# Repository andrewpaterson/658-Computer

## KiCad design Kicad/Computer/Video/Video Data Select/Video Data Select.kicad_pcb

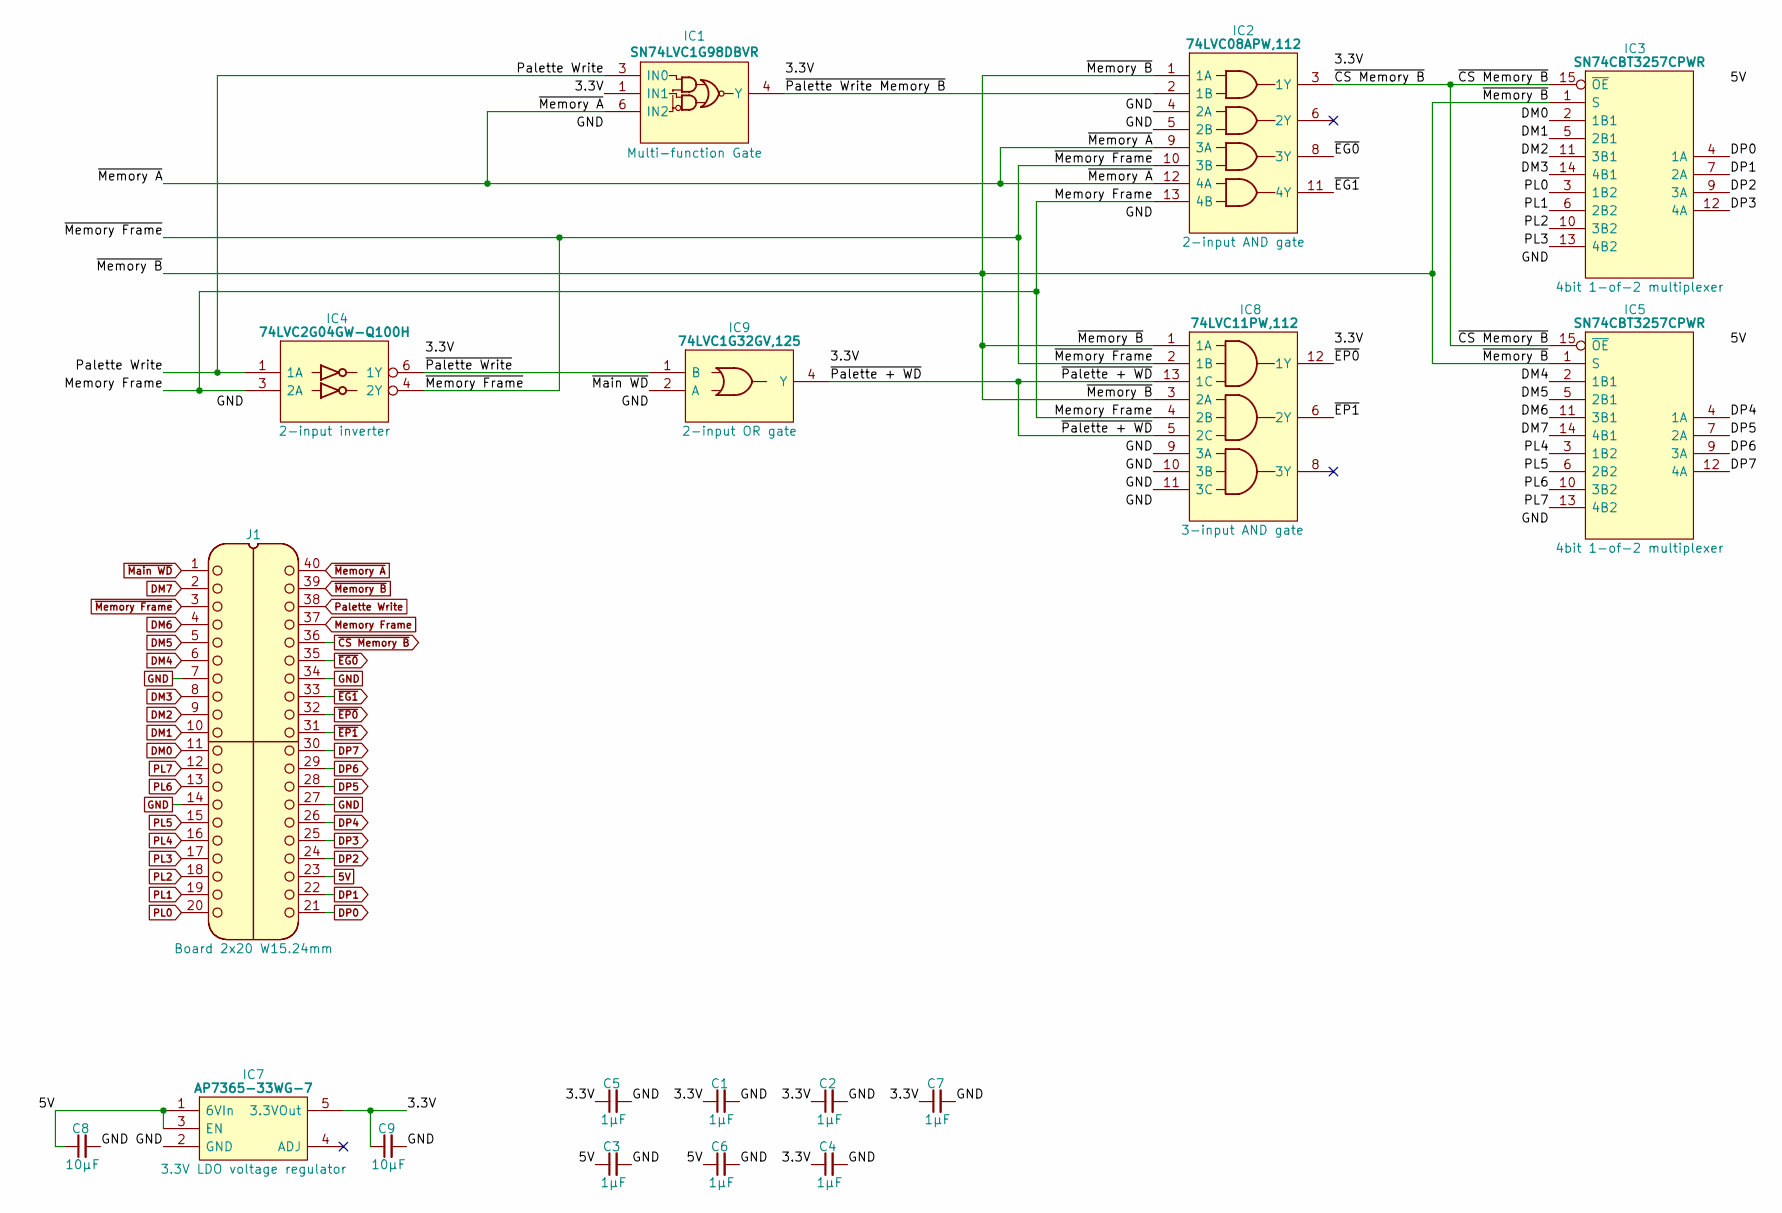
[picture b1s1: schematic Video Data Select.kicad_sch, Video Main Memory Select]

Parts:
C1, C2, C3, C4, C5, C6, C7: 1μF; C_0805
C8, C9: 10μF; C_0805
IC1: SN74LVC1G98DBVR; SOT95P280X145-6N; Manufacturer_Part_Number SN74LVC1G98DBVR; Mouser Part Number 595-SN74LVC1G98DBVR
IC2: 74LVC08APW,112; SOP65P640X110-14N; Manufacturer_Part_Number 74LVC08APW,112; Mouser Part Number 771-74LVC08APW
IC3, IC5: SN74CBT3257CPWR; SOP65P640X120-16N; Manufacturer_Part_Number SN74CBT3257CPWR; Mouser Part Number 595-SN74CBT3257CPWR
IC4: 74LVC2G04GW-Q100H; SOP65P210X110-6N; Manufacturer_Part_Number 74LVC2G04GW-Q100H; Mouser Part Number 771-74LVC2G04GWQ100H
IC7: AP7365-33WG-7; SOT95P285X130-5N; Manufacturer_Part_Number AP7365-33WG-7; Mouser Part Number 621-AP7365-33WG-7
IC8: 74LVC11PW,112; SOP65P640X110-14N; Mouser Part Number 771-LVC11PW112
IC9: 74LVC1G32GV,125; SOT95P275X110-5N; Manufacturer_Part_Number 74LVC1G32GV,125; Mouser Part Number 771-LVC1G32GV125
J1: Board 2x20 W15.24mm; DIP-40_Board_W15.24mm

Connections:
5V: C3.1, C6.1, C8.1, IC3.16 (5V), IC5.16 (5V), IC7.1 (6VIn), IC7.3 (EN), J1.23
/3.3V: C1.1, C2.1, C4.1, C5.1, C7.1, C9.1, IC1.1 (IN1), IC1.5 (3V), IC2.14 (3V), IC4.5 (3V), IC7.5 (3.3VOut), IC8.14 (3V), IC9.5 (3V)
/~Palette + WD: IC8.5 (2C), IC8.13 (1C), IC9.4 (Y)
/~Palette Write Memory B: IC1.4 (Y), IC2.2 (1B)
/~Palette Write: IC4.6 (1Y), IC9.1 (B)
DM0: IC3.2 (1B1), J1.11
DM1: IC3.5 (2B1), J1.10
DM2: IC3.11 (3B1), J1.9
DM3: IC3.14 (4B1), J1.8
DM4: IC5.2 (1B1), J1.6
DM5: IC5.5 (2B1), J1.5
DM6: IC5.11 (3B1), J1.4
DM7: IC5.14 (4B1), J1.2
DP0: IC3.4 (1A), J1.21
DP1: IC3.7 (2A), J1.22
DP2: IC3.9 (3A), J1.24
DP3: IC3.12 (4A), J1.25
DP4: IC5.4 (1A), J1.26
DP5: IC5.7 (2A), J1.28
DP6: IC5.9 (3A), J1.29
DP7: IC5.12 (4A), J1.30
GND: C1.2, C2.2, C3.2, C4.2, C5.2, C6.2, C7.2, C8.2, C9.2, IC1.2 (GND), IC2.4 (2A), IC2.5 (2B), IC2.7 (GND), IC3.8 (GND), IC4.2 (GND), IC5.8 (GND), IC7.2 (GND), IC8.7 (GND), IC8.9 (3A), IC8.10 (3B), IC8.11 (3C), IC9.3 (GND), J1.7, J1.14, J1.27, J1.34
Memory Frame: IC2.13 (4B), IC4.3 (2A), IC8.4 (2B), J1.37
PL0: IC3.3 (1B2), J1.20
PL1: IC3.6 (2B2), J1.19
PL2: IC3.10 (3B2), J1.18
PL3: IC3.13 (4B2), J1.17
PL4: IC5.3 (1B2), J1.16
PL5: IC5.6 (2B2), J1.15
PL6: IC5.10 (3B2), J1.13
PL7: IC5.13 (4B2), J1.12
Palette Write: IC1.3 (IN0), IC4.1 (1A), J1.38
~CS Memory B: IC2.3 (1Y), IC3.15 (~OE), IC5.15 (~OE), J1.36
~EG0: IC2.8 (3Y), J1.35
~EG1: IC2.11 (4Y), J1.33
~EP0: IC8.12 (1Y), J1.32
~EP1: IC8.6 (2Y), J1.31
~Main WD: IC9.2 (A), J1.1
~Memory A: IC1.6 (IN2), IC2.9 (3A), IC2.12 (4A), J1.40
~Memory B: IC2.1 (1A), IC3.1 (S), IC5.1 (S), IC8.1 (1A), IC8.3 (2A), J1.39
~Memory Frame: IC2.10 (3B), IC4.4 (2Y), IC8.2 (1B), J1.3

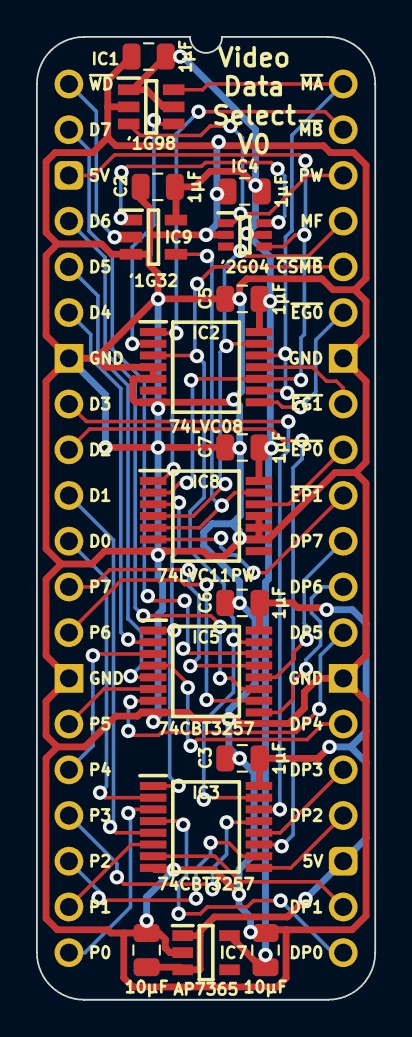
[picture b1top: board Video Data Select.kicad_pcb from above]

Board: 2 copper layers, 18.8 x 53.5 mm, 18 parts (0 on the bottom side), 41 nets.

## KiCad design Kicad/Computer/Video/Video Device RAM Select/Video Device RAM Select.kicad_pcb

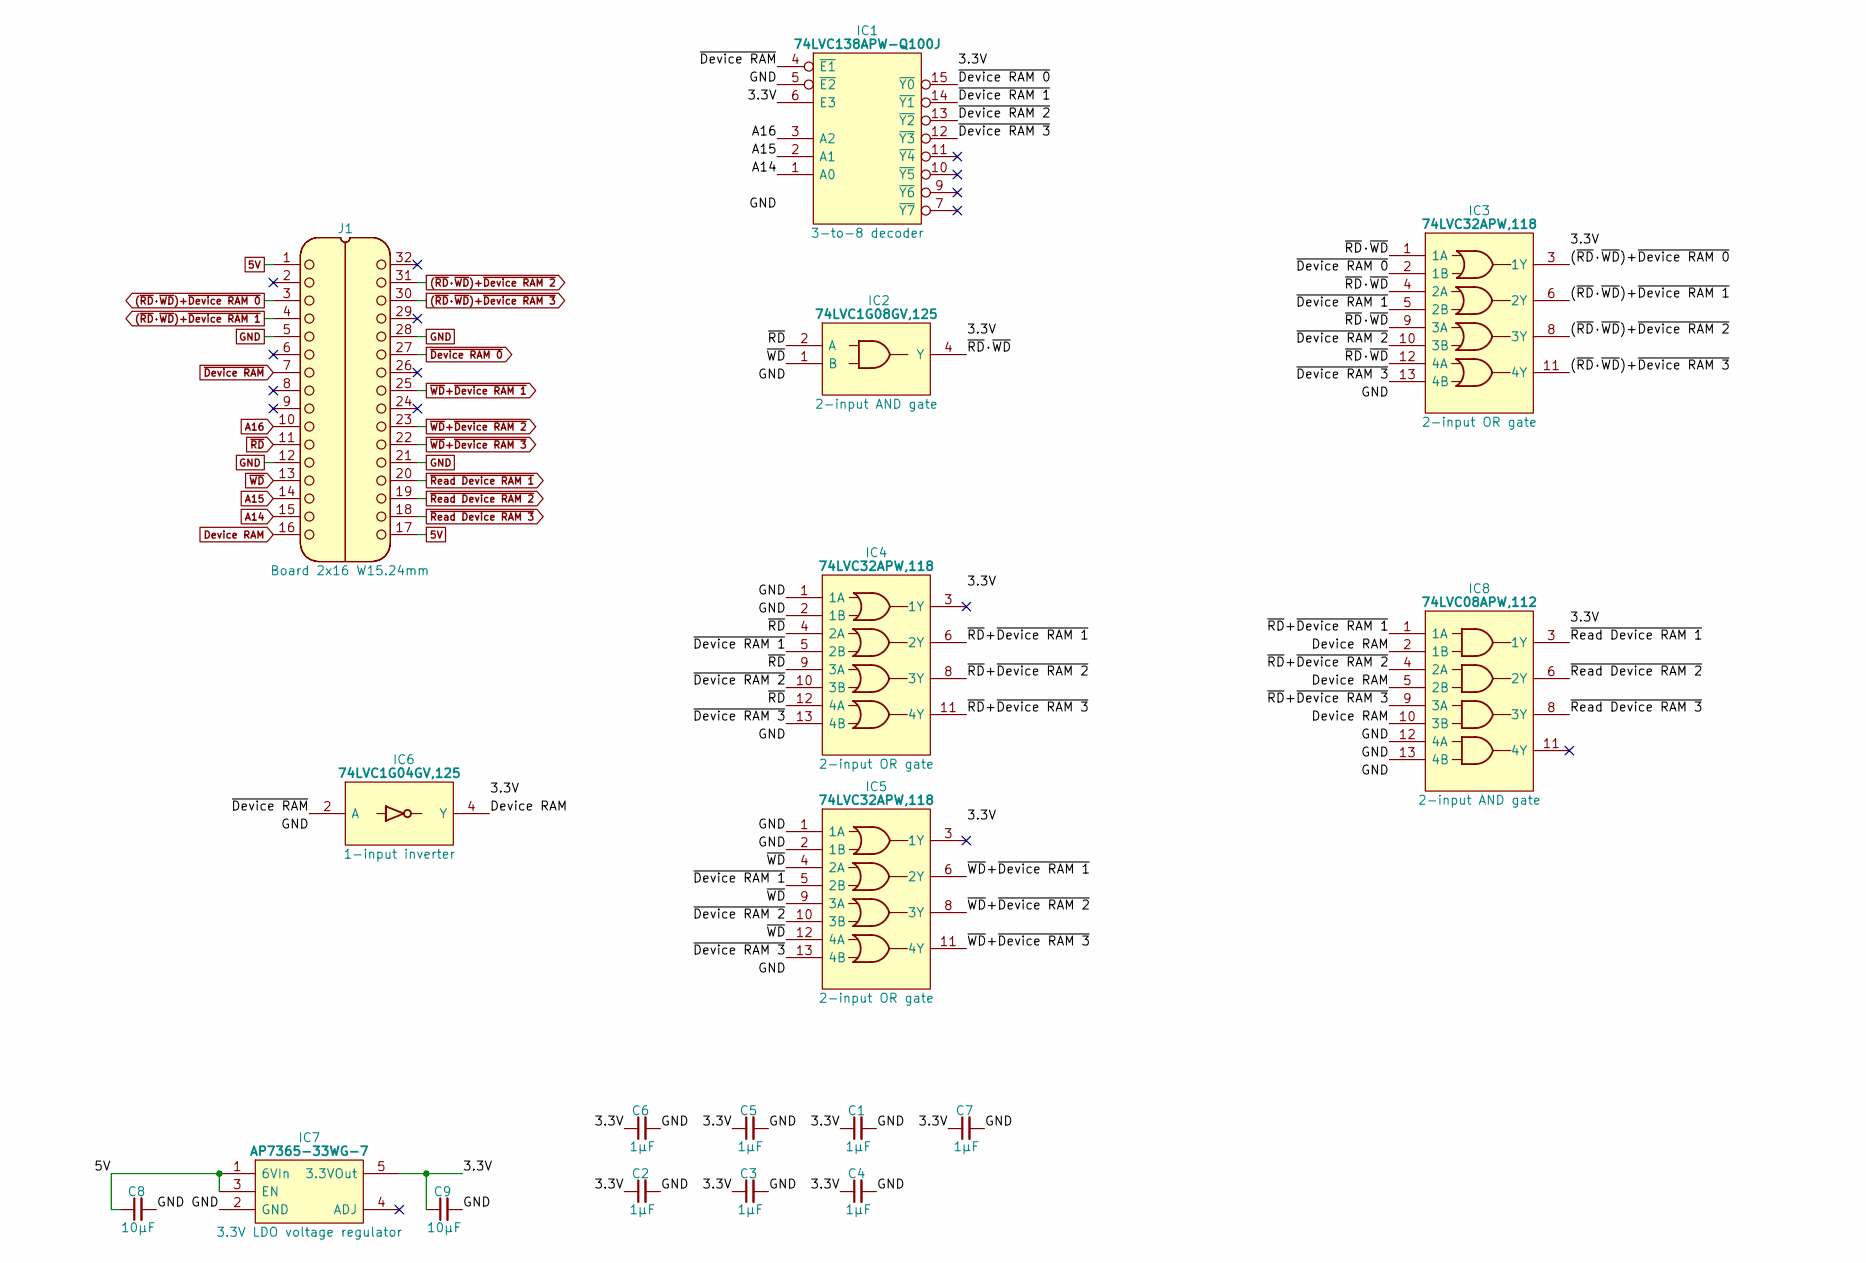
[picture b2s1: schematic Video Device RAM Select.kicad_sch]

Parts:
C1, C2, C3, C4, C5, C6, C7: 1μF; C_0805
C8, C9: 10µF; C_0805
IC1: 74LVC138APW-Q100J; SOP65P640X110-16N; Mouser Part Number 771-74LVC138APWQ100J
IC2: 74LVC1G08GV,125; SOT95P275X110-5N; Manufacturer_Part_Number 74LVC1G08GV,125; Mouser Part Number 771-74LVC1G08GV
IC3, IC4, IC5: 74LVC32APW,118; SOP65P640X110-14N; Manufacturer_Part_Number 74LVC32APW,118; Mouser Part Number 771-74LVC32APW-T
IC6: 74LVC1G04GV,125; SOT95P275X110-5N; Manufacturer_Part_Number 74LVC1G04GV,125; Mouser Part Number 771-74LVC1G04GV
IC7: AP7365-33WG-7; SOT95P285X130-5N; Manufacturer_Part_Number AP7365-33WG-7; Mouser Part Number 621-AP7365-33WG-7
IC8: 74LVC08APW,112; SOP65P640X110-14N; Manufacturer_Part_Number 74LVC08APW,112; Mouser Part Number 771-74LVC08APW
J1: Board 2x16 W15.24mm; DIP-32_Board_W15.24mm

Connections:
5V: C8.1, IC7.1 (6VIn), IC7.3 (EN), J1.1, J1.17
(~RD·~WD)+~Device RAM 0: IC3.3 (1Y), J1.3
(~RD·~WD)+~Device RAM 1: IC3.6 (2Y), J1.4
(~RD·~WD)+~Device RAM 2: IC3.8 (3Y), J1.31
(~RD·~WD)+~Device RAM 3: IC3.11 (4Y), J1.30
/3.3V: C1.1, C2.1, C3.1, C4.1, C5.1, C6.1, C7.1, C9.1, IC1.6 (E3), IC1.16 (3V), IC2.5 (3V), IC3.14 (3V), IC4.14 (3V), IC5.14 (3V), IC6.5 (3V), IC7.5 (3.3VOut), IC8.14 (3V)
/~Device RAM 1: IC1.14 (~Y1), IC3.5 (2B), IC4.5 (2B), IC5.5 (2B)
/~Device RAM 2: IC1.13 (~Y2), IC3.10 (3B), IC4.10 (3B), IC5.10 (3B)
/~Device RAM 3: IC1.12 (~Y3), IC3.13 (4B), IC4.13 (4B), IC5.13 (4B)
/~RD+~Device RAM 1: IC4.6 (2Y), IC8.1 (1A)
/~RD+~Device RAM 2: IC4.8 (3Y), IC8.4 (2A)
/~RD+~Device RAM 3: IC4.11 (4Y), IC8.9 (3A)
/~RD·~WD: IC2.4 (Y), IC3.1 (1A), IC3.4 (2A), IC3.9 (3A), IC3.12 (4A)
A14: IC1.1 (A0), J1.15
A15: IC1.2 (A1), J1.14
A16: IC1.3 (A2), J1.10
Device RAM: IC6.4 (Y), IC8.2 (1B), IC8.5 (2B), IC8.10 (3B), J1.16
GND: C1.2, C2.2, C3.2, C4.2, C5.2, C6.2, C7.2, C8.2, C9.2, IC1.5 (~E2), IC1.8 (GND), IC2.3 (GND), IC3.7 (GND), IC4.1 (1A), IC4.2 (1B), IC4.7 (GND), IC5.1 (1A), IC5.2 (1B), IC5.7 (GND), IC6.3 (GND), IC7.2 (GND), IC8.7 (GND), IC8.12 (4A), IC8.13 (4B), J1.5, J1.12, J1.21, J1.28
~Device RAM 0: IC1.15 (~Y0), IC3.2 (1B), J1.27
~Device RAM: IC1.4 (~E1), IC6.2 (A), J1.7
~RD: IC2.2 (A), IC4.4 (2A), IC4.9 (3A), IC4.12 (4A), J1.11
~Read Device RAM 1: IC8.3 (1Y), J1.20
~Read Device RAM 2: IC8.6 (2Y), J1.19
~Read Device RAM 3: IC8.8 (3Y), J1.18
~WD: IC2.1 (B), IC5.4 (2A), IC5.9 (3A), IC5.12 (4A), J1.13
~WD+~Device RAM 1: IC5.6 (2Y), J1.25
~WD+~Device RAM 2: IC5.8 (3Y), J1.23
~WD+~Device RAM 3: IC5.11 (4Y), J1.22

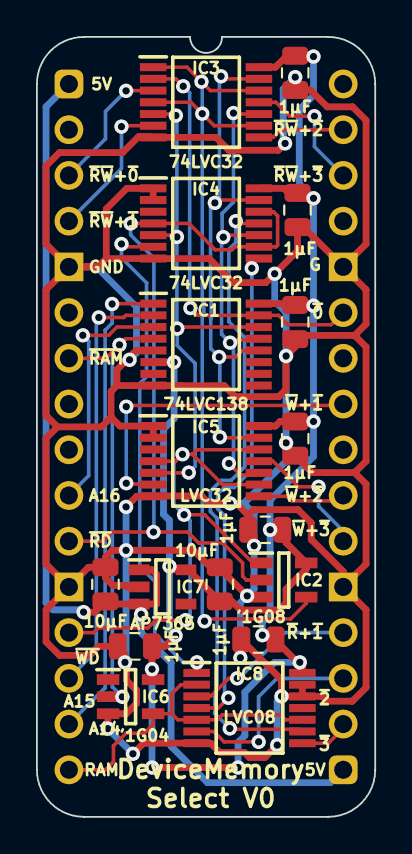
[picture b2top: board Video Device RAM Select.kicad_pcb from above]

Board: 2 copper layers, 18.8 x 43.3 mm, 18 parts (0 on the bottom side), 28 nets.

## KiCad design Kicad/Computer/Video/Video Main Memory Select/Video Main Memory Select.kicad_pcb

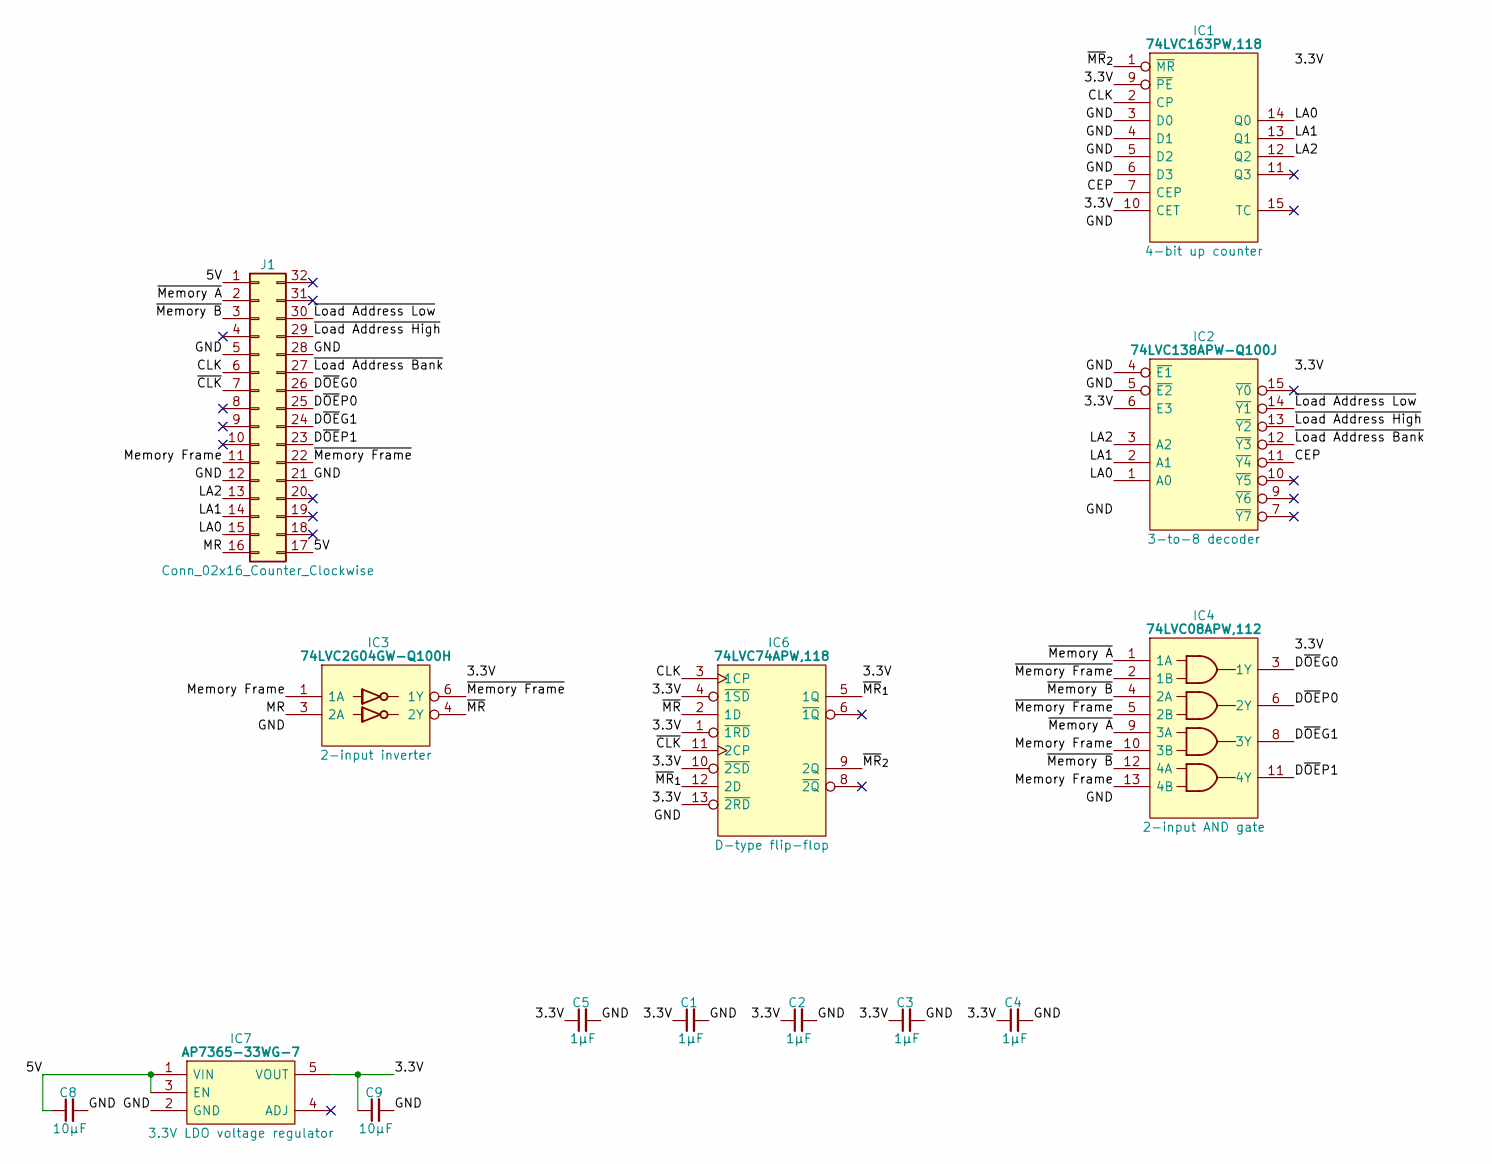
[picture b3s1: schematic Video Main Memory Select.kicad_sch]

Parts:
C1, C2, C3, C4, C5: 1μF; C_0805
C8, C9: 10µF; C_0805
IC1: 74LVC163PW,118; SOP65P640X110-16N; Mouser Part Number 771-74LVC163PW-T
IC2: 74LVC138APW-Q100J; SOP65P640X110-16N; Mouser Part Number 771-74LVC138APWQ100J
IC3: 74LVC2G04GW-Q100H; SOP65P210X110-6N; Manufacturer_Part_Number 74LVC2G04GW-Q100H; Mouser Part Number 771-74LVC2G04GWQ100H
IC4: 74LVC08APW,112; SOP65P640X110-14N; Manufacturer_Part_Number 74LVC08APW,112; Mouser Part Number 771-74LVC08APW
IC6: 74LVC74APW,118; SOP65P640X110-14N; Mouser Part Number 771-74LVC74APW-T
IC7: AP7365-33WG-7; SOT95P285X130-5N; Manufacturer_Part_Number AP7365-33WG-7; Mouser Part Number 621-AP7365-33WG-7
J1: Conn_02x16_Counter_Clockwise; DIP-32_Board_W15.24mm

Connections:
/3.3V: C1.1, C2.1, C3.1, C4.1, C5.1, C9.1, IC1.9 (~PE), IC1.10 (CET), IC1.16 (3V), IC2.6 (E3), IC2.16 (3V), IC3.5 (3V), IC4.14 (3V), IC6.1 (~1RD), IC6.4 (~1SD), IC6.10 (~2SD), IC6.13 (~2RD), IC6.14 (3V), IC7.5 (VOUT)
/5V: C8.1, IC7.1 (VIN), IC7.3 (EN), J1.1, J1.17
/CEP: IC1.7 (CEP), IC2.11 (~Y4)
/CLK: IC1.2 (CP), IC6.3 (1CP), J1.6
/D~OEG0: IC4.3 (1Y), J1.26
/D~OEG1: IC4.8 (3Y), J1.24
/D~OEP0: IC4.6 (2Y), J1.25
/D~OEP1: IC4.11 (4Y), J1.23
/GND: C1.2, C2.2, C3.2, C4.2, C5.2, C8.2, C9.2, IC1.3 (D0), IC1.4 (D1), IC1.5 (D2), IC1.6 (D3), IC1.8 (GND), IC2.4 (~E1), IC2.5 (~E2), IC2.8 (GND), IC3.2 (GND), IC4.7 (GND), IC6.7 (GND), IC7.2 (GND), J1.5, J1.12, J1.21, J1.28
/LA0: IC1.14 (Q0), IC2.1 (A0), J1.15
/LA1: IC1.13 (Q1), IC2.2 (A1), J1.14
/LA2: IC1.12 (Q2), IC2.3 (A2), J1.13
/MR: IC3.3 (2A), J1.16
/Memory Frame: IC3.1 (1A), IC4.10 (3B), IC4.13 (4B), J1.11
/~CLK: IC6.11 (2CP), J1.7
/~Load Address Bank: IC2.12 (~Y3), J1.27
/~Load Address High: IC2.13 (~Y2), J1.29
/~Load Address Low: IC2.14 (~Y1), J1.30
/~MR: IC3.4 (2Y), IC6.2 (1D)
/~MR_{1}: IC6.5 (1Q), IC6.12 (2D)
/~MR_{2}: IC1.1 (~MR), IC6.9 (2Q)
/~Memory A: IC4.1 (1A), IC4.9 (3A), J1.2
/~Memory B: IC4.4 (2A), IC4.12 (4A), J1.3
/~Memory Frame: IC3.6 (1Y), IC4.2 (1B), IC4.5 (2B), J1.22

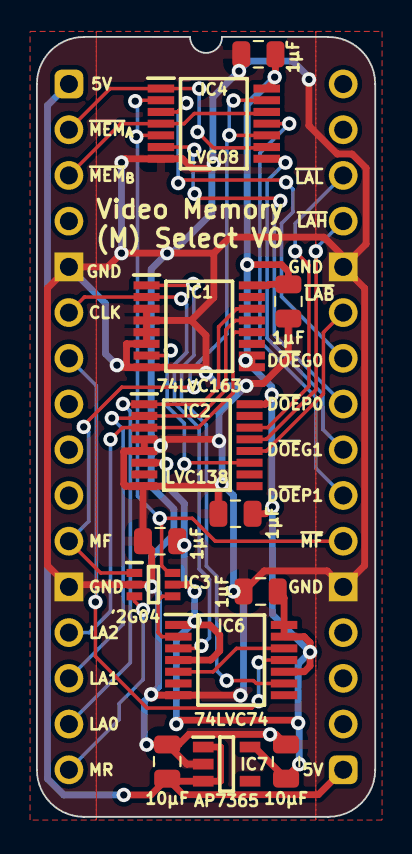
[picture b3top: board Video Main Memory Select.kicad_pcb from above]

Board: 2 copper layers, 18.8 x 43.3 mm, 14 parts (0 on the bottom side), 24 nets.

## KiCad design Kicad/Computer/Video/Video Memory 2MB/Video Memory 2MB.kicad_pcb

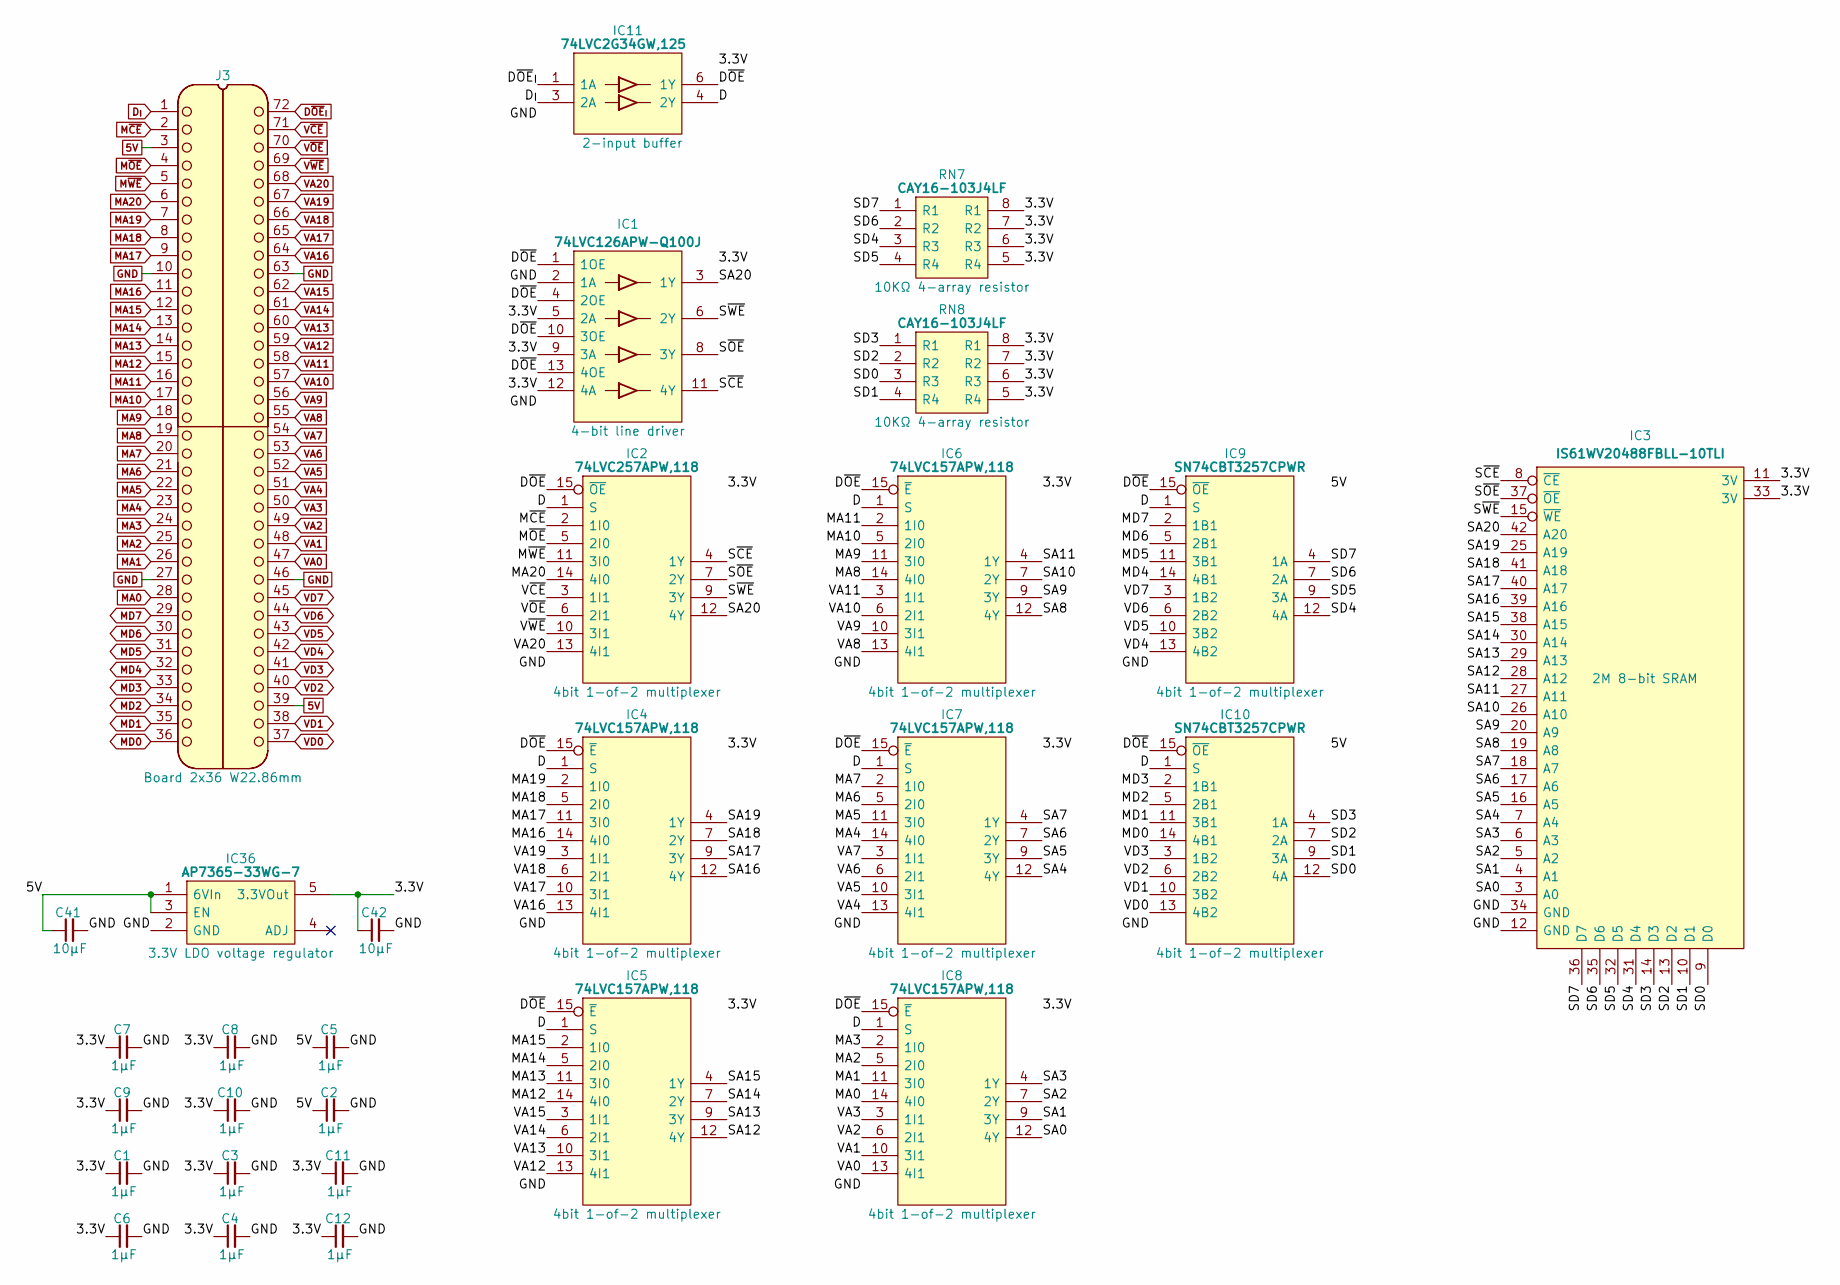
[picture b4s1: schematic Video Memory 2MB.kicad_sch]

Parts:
C1, C2, C3, C4, C5, C6, C7, C8, C9, C10, C11, C12: 1μF; C_0805
C41, C42: 10μF; C_0805
IC1: 74LVC126APW-Q100J; SOP65P640X110-14N; Mouser Part Number 771-74LVC126APW-Q100J
IC2: 74LVC257APW,118; SOP65P640X110-16N; Manufacturer_Part_Number 74LVC257APW,118; Mouser Part Number 771-74LVC257APW-T
IC3: IS61WV20488FBLL-10TLI; SOP80P1176X120-44N; Mouser Part Number 870-61W20488FBLL10TI
IC4, IC5, IC6, IC7, IC8: 74LVC157APW,118; SOP65P640X110-16N; Manufacturer_Part_Number 74LVC157APW,118; Mouser Part Number 771-74LVC157APW-T
IC9, IC10: SN74CBT3257CPWR; SOP65P640X120-16N; Manufacturer_Part_Number SN74CBT3257CPWR; Mouser Part Number 595-SN74CBT3257CPWR
IC11: 74LVC2G34GW,125; 74LVC2G34GW125; Manufacturer_Part_Number 74LVC2G34GW,125; Mouser Part Number 771-LVC2G34GW125
IC36: AP7365-33WG-7; SOT95P285X130-5N; Manufacturer_Part_Number AP7365-33WG-7; Mouser Part Number 621-AP7365-33WG-7
J3: Board 2x36 W22.86mm; DIP-72_Board_W22.86mm
RN7, RN8: CAY16-103J4LF; CAY16-J4; Manufacturer_Part_Number CAY16-103J4LF; Mouser Part Number 652-CAY16-103J4LF

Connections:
5V: C2.1, C5.1, C41.1, IC9.16 (5V), IC10.16 (5V), IC36.1 (6VIn), IC36.3 (EN), J3.3, J3.39
/3.3V: C1.1, C3.1, C4.1, C6.1, C7.1, C8.1, C9.1, C10.1, C11.1, C12.1, C42.1, IC1.5 (2A), IC1.9 (3A), IC1.12 (4A), IC1.14 (3V), IC2.16 (3V), IC3.11 (3V), IC3.33 (3V), IC4.16 (3V), IC5.16 (3V), IC6.16 (3V), IC7.16 (3V), IC8.16 (3V), IC11.5 (3V), IC36.5 (3.3VOut), RN7.5 (R4), RN7.6 (R3), RN7.7 (R2), RN7.8 (R1), RN8.5 (R4), RN8.6 (R3), RN8.7 (R2), RN8.8 (R1)
/D: IC2.1 (S), IC4.1 (S), IC5.1 (S), IC6.1 (S), IC7.1 (S), IC8.1 (S), IC9.1 (S), IC10.1 (S), IC11.4 (2Y)
/D~OE: IC1.1 (1OE), IC1.4 (2OE), IC1.10 (3OE), IC1.13 (4OE), IC2.15 (~OE), IC4.15 (~E), IC5.15 (~E), IC6.15 (~E), IC7.15 (~E), IC8.15 (~E), IC9.15 (~OE), IC10.15 (~OE), IC11.6 (1Y)
/SA0: IC3.3 (A0), IC8.12 (4Y)
/SA1: IC3.4 (A1), IC8.9 (3Y)
/SA2: IC3.5 (A2), IC8.7 (2Y)
/SA3: IC3.6 (A3), IC8.4 (1Y)
/SA4: IC3.7 (A4), IC7.12 (4Y)
/SA5: IC3.16 (A5), IC7.9 (3Y)
/SA6: IC3.17 (A6), IC7.7 (2Y)
/SA7: IC3.18 (A7), IC7.4 (1Y)
/SA8: IC3.19 (A8), IC6.12 (4Y)
/SA9: IC3.20 (A9), IC6.9 (3Y)
/SA10: IC3.26 (A10), IC6.7 (2Y)
/SA11: IC3.27 (A11), IC6.4 (1Y)
/SA12: IC3.28 (A12), IC5.12 (4Y)
/SA13: IC3.29 (A13), IC5.9 (3Y)
/SA14: IC3.30 (A14), IC5.7 (2Y)
/SA15: IC3.38 (A15), IC5.4 (1Y)
/SA16: IC3.39 (A16), IC4.12 (4Y)
/SA17: IC3.40 (A17), IC4.9 (3Y)
/SA18: IC3.41 (A18), IC4.7 (2Y)
/SA19: IC3.25 (A19), IC4.4 (1Y)
/SA20: IC1.3 (1Y), IC2.12 (4Y), IC3.42 (A20)
/SD0: IC3.9 (D0), IC10.12 (4A), RN8.3 (R3)
/SD1: IC3.10 (D1), IC10.9 (3A), RN8.4 (R4)
/SD2: IC3.13 (D2), IC10.7 (2A), RN8.2 (R2)
/SD3: IC3.14 (D3), IC10.4 (1A), RN8.1 (R1)
/SD4: IC3.31 (D4), IC9.12 (4A), RN7.3 (R3)
/SD5: IC3.32 (D5), IC9.9 (3A), RN7.4 (R4)
/SD6: IC3.35 (D6), IC9.7 (2A), RN7.2 (R2)
/SD7: IC3.36 (D7), IC9.4 (1A), RN7.1 (R1)
/S~CE: IC1.11 (4Y), IC2.4 (1Y), IC3.8 (~CE)
/S~OE: IC1.8 (3Y), IC2.7 (2Y), IC3.37 (~OE)
/S~WE: IC1.6 (2Y), IC2.9 (3Y), IC3.15 (~WE)
D_{I}: IC11.3 (2A), J3.1
D~OE_{I}: IC11.1 (1A), J3.72
GND: C1.2, C2.2, C3.2, C4.2, C5.2, C6.2, C7.2, C8.2, C9.2, C10.2, C11.2, C12.2, C41.2, C42.2, IC1.2 (1A), IC1.7 (GND), IC2.8 (GND), IC3.12 (GND), IC3.34 (GND), IC4.8 (GND), IC5.8 (GND), IC6.8 (GND), IC7.8 (GND), IC8.8 (GND), IC9.8 (GND), IC10.8 (GND), IC11.2 (GND), IC36.2 (GND), J3.10, J3.27, J3.46, J3.63
MA0: IC8.14 (4I0), J3.28
MA1: IC8.11 (3I0), J3.26
MA2: IC8.5 (2I0), J3.25
MA3: IC8.2 (1I0), J3.24
MA4: IC7.14 (4I0), J3.23
MA5: IC7.11 (3I0), J3.22
MA6: IC7.5 (2I0), J3.21
MA7: IC7.2 (1I0), J3.20
MA8: IC6.14 (4I0), J3.19
MA9: IC6.11 (3I0), J3.18
MA10: IC6.5 (2I0), J3.17
MA11: IC6.2 (1I0), J3.16
MA12: IC5.14 (4I0), J3.15
MA13: IC5.11 (3I0), J3.14
MA14: IC5.5 (2I0), J3.13
MA15: IC5.2 (1I0), J3.12
MA16: IC4.14 (4I0), J3.11
MA17: IC4.11 (3I0), J3.9
MA18: IC4.5 (2I0), J3.8
MA19: IC4.2 (1I0), J3.7
MA20: IC2.14 (4I0), J3.6
MD0: IC10.14 (4B1), J3.36
MD1: IC10.11 (3B1), J3.35
MD2: IC10.5 (2B1), J3.34
MD3: IC10.2 (1B1), J3.33
MD4: IC9.14 (4B1), J3.32
MD5: IC9.11 (3B1), J3.31
MD6: IC9.5 (2B1), J3.30
MD7: IC9.2 (1B1), J3.29
M~CE: IC2.2 (1I0), J3.2
M~OE: IC2.5 (2I0), J3.4
M~WE: IC2.11 (3I0), J3.5
VA0: IC8.13 (4I1), J3.47
VA1: IC8.10 (3I1), J3.48
VA2: IC8.6 (2I1), J3.49
VA3: IC8.3 (1I1), J3.50
VA4: IC7.13 (4I1), J3.51
VA5: IC7.10 (3I1), J3.52
VA6: IC7.6 (2I1), J3.53
VA7: IC7.3 (1I1), J3.54
VA8: IC6.13 (4I1), J3.55
VA9: IC6.10 (3I1), J3.56
VA10: IC6.6 (2I1), J3.57
VA11: IC6.3 (1I1), J3.58
VA12: IC5.13 (4I1), J3.59
VA13: IC5.10 (3I1), J3.60
VA14: IC5.6 (2I1), J3.61
VA15: IC5.3 (1I1), J3.62
VA16: IC4.13 (4I1), J3.64
VA17: IC4.10 (3I1), J3.65
VA18: IC4.6 (2I1), J3.66
VA19: IC4.3 (1I1), J3.67
VA20: IC2.13 (4I1), J3.68
VD0: IC10.13 (4B2), J3.37
VD1: IC10.10 (3B2), J3.38
VD2: IC10.6 (2B2), J3.40
VD3: IC10.3 (1B2), J3.41
VD4: IC9.13 (4B2), J3.42
VD5: IC9.10 (3B2), J3.43
VD6: IC9.6 (2B2), J3.44
VD7: IC9.3 (1B2), J3.45
V~CE: IC2.3 (1I1), J3.71
V~OE: IC2.6 (2I1), J3.70
V~WE: IC2.10 (3I1), J3.69

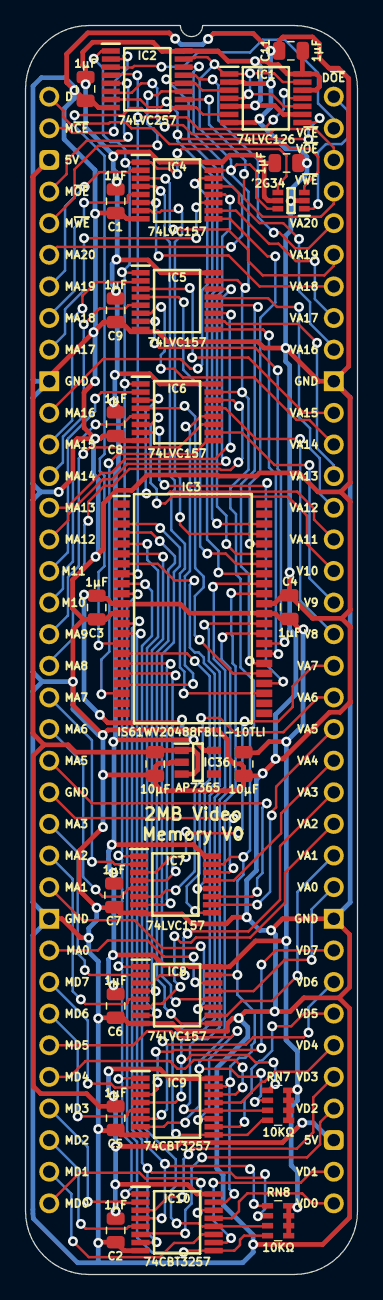
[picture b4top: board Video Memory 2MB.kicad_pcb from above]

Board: 2 copper layers, 26.7 x 100.3 mm, 29 parts (0 on the bottom side), 103 nets.

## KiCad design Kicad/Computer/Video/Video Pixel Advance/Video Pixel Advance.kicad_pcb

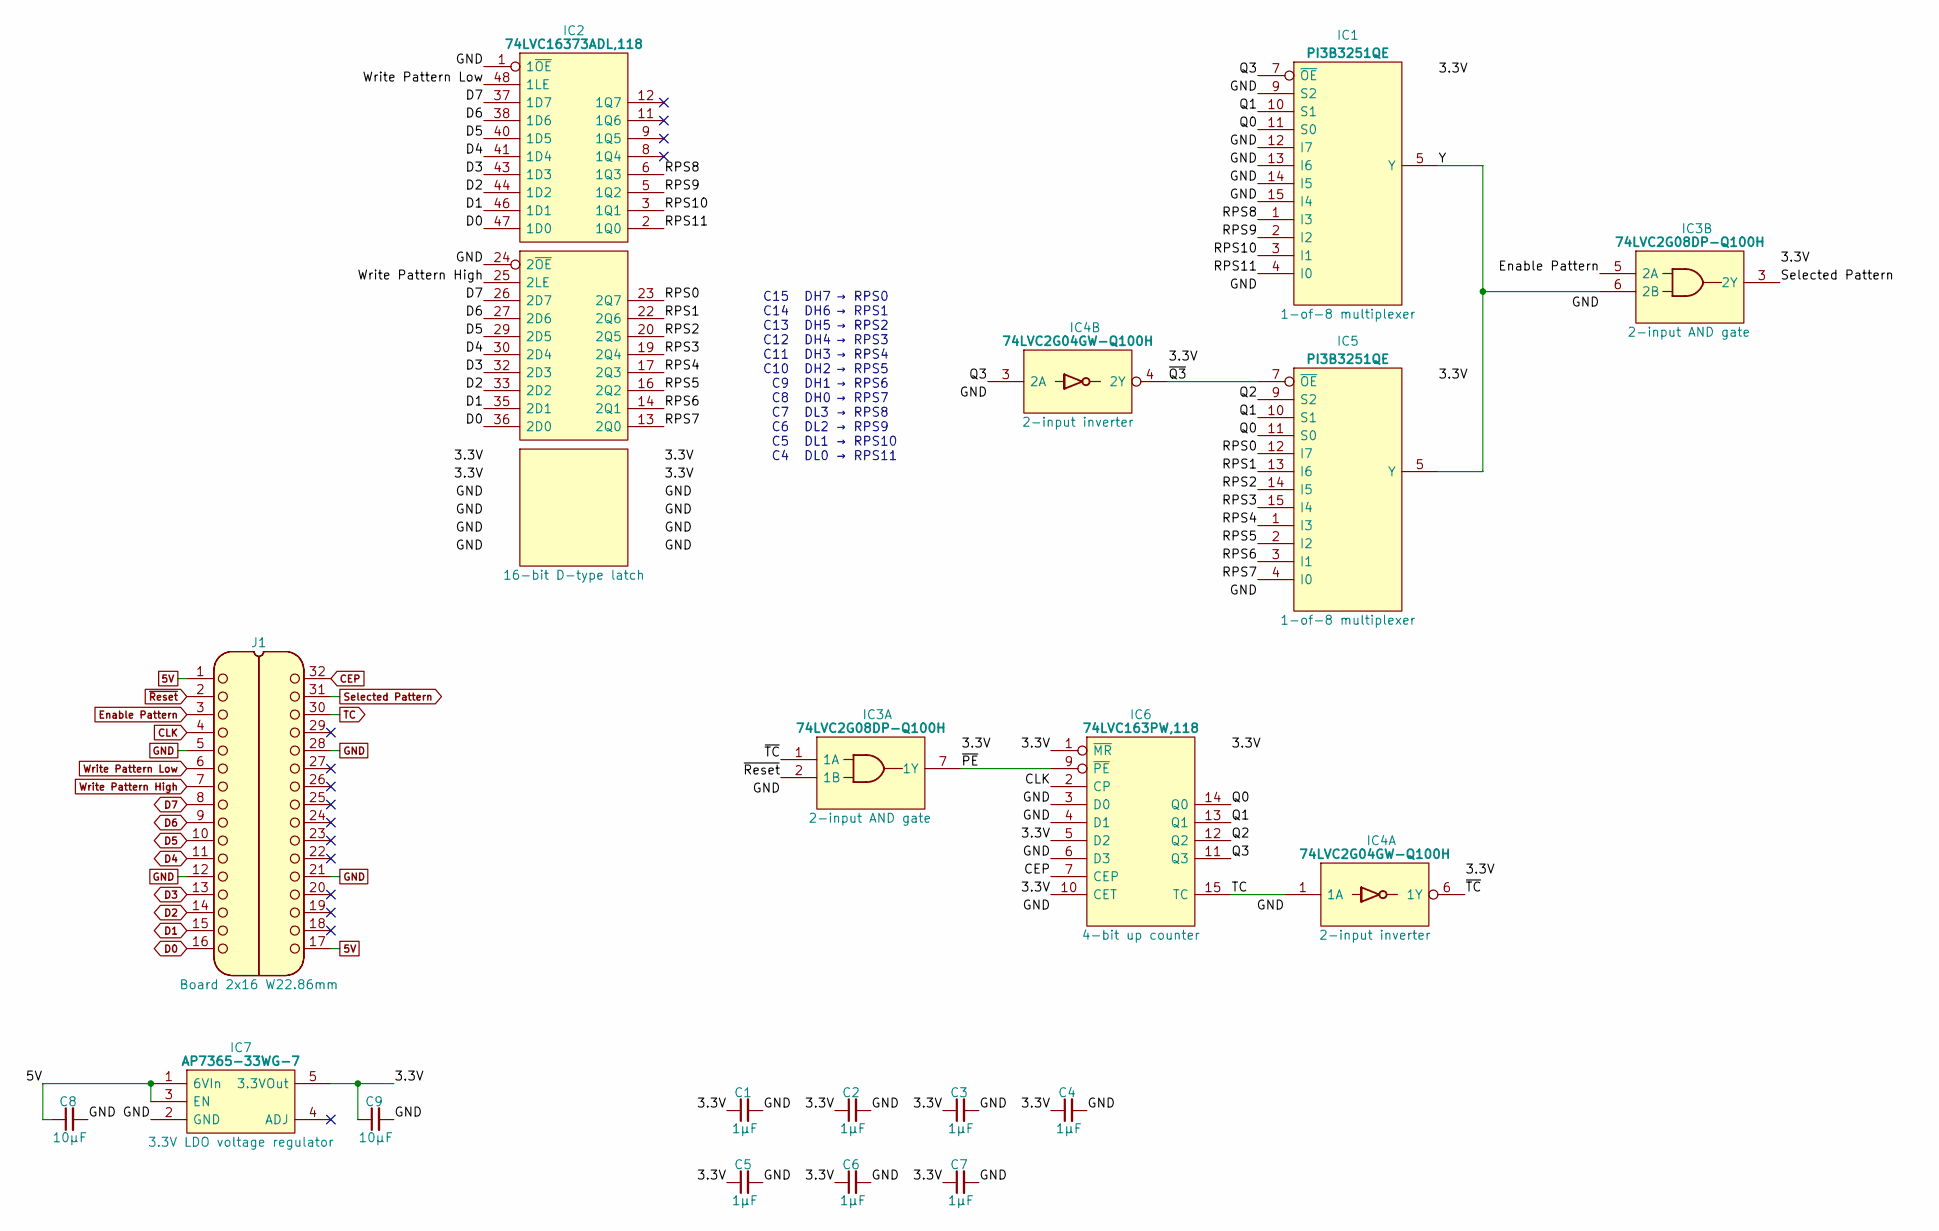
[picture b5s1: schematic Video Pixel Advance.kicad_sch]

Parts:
C1, C2, C3, C4, C5, C6, C7: 1μF; C_0805
C8, C9: 10µF; C_0805
IC1, IC5: PI3B3251QE; SOP64P599X175-16N; Manufacturer_Part_Number PI3B3251QE; Mouser Part Number 729-PI3B3251QE
IC2: 74LVC16373ADL,118; SOP64P1025X280-48N; Mouser Part Number 771-LVC16373ADL118
IC3: 74LVC2G08DP-Q100H; SOP65P400X110-8N; Manufacturer_Part_Number 74LVC2G08DP-Q100H; Mouser Part Number 771-74LVC2G08DPQ100H
IC4: 74LVC2G04GW-Q100H; SOP65P210X110-6N; Manufacturer_Part_Number 74LVC2G04GW-Q100H; Mouser Part Number 771-74LVC2G04GWQ100H
IC6: 74LVC163PW,118; SOP65P640X110-16N; Mouser Part Number 771-74LVC163PW-T
IC7: AP7365-33WG-7; SOT95P285X130-5N; Manufacturer_Part_Number AP7365-33WG-7; Mouser Part Number 621-AP7365-33WG-7
J1: Board 2x16 W22.86mm; DIP-32_Board_W22.86mm

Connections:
5V: C8.1, IC7.1 (6VIn), IC7.3 (EN), J1.1, J1.17
/3.3V: C1.1, C2.1, C3.1, C4.1, C5.1, C6.1, C7.1, C9.1, IC1.16 (3V), IC2.7 (3V), IC2.18 (3V), IC2.31 (3V), IC2.42 (3V), IC3.8 (3V), IC4.5 (3V), IC5.16 (3V), IC6.1 (~MR), IC6.5 (D2), IC6.10 (CET), IC6.16 (3V), IC7.5 (3.3VOut)
/Q0: IC1.11 (S0), IC5.11 (S0), IC6.14 (Q0)
/Q1: IC1.10 (S1), IC5.10 (S1), IC6.13 (Q1)
/Q2: IC5.9 (S2), IC6.12 (Q2)
/Q3: IC1.7 (~OE), IC4.3 (2A), IC6.11 (Q3)
/RPS0: IC2.23 (2Q7), IC5.12 (I7)
/RPS1: IC2.22 (2Q6), IC5.13 (I6)
/RPS2: IC2.20 (2Q5), IC5.14 (I5)
/RPS3: IC2.19 (2Q4), IC5.15 (I4)
/RPS4: IC2.17 (2Q3), IC5.1 (I3)
/RPS5: IC2.16 (2Q2), IC5.2 (I2)
/RPS6: IC2.14 (2Q1), IC5.3 (I1)
/RPS7: IC2.13 (2Q0), IC5.4 (I0)
/RPS8: IC1.1 (I3), IC2.6 (1Q3)
/RPS9: IC1.2 (I2), IC2.5 (1Q2)
/RPS10: IC1.3 (I1), IC2.3 (1Q1)
/RPS11: IC1.4 (I0), IC2.2 (1Q0)
/Y: IC1.5 (Y), IC3.6 (2B), IC5.5 (Y)
/~PE: IC3.7 (1Y), IC6.9 (~PE)
/~Q3: IC4.4 (2Y), IC5.7 (~OE)
/~TC: IC3.1 (1A), IC4.6 (1Y)
CEP: IC6.7 (CEP), J1.32
CLK: IC6.2 (CP), J1.4
D0: IC2.36 (2D0), IC2.47 (1D0), J1.16
D1: IC2.35 (2D1), IC2.46 (1D1), J1.15
D2: IC2.33 (2D2), IC2.44 (1D2), J1.14
D3: IC2.32 (2D3), IC2.43 (1D3), J1.13
D4: IC2.30 (2D4), IC2.41 (1D4), J1.11
D5: IC2.29 (2D5), IC2.40 (1D5), J1.10
D6: IC2.27 (2D6), IC2.38 (1D6), J1.9
D7: IC2.26 (2D7), IC2.37 (1D7), J1.8
Enable Pattern: IC3.5 (2A), J1.3
GND: C1.2, C2.2, C3.2, C4.2, C5.2, C6.2, C7.2, C8.2, C9.2, IC1.8 (GND), IC1.9 (S2), IC1.12 (I7), IC1.13 (I6), IC1.14 (I5), IC1.15 (I4), IC2.1 (1~OE), IC2.4 (GND), IC2.10 (GND), IC2.15 (GND), IC2.21 (GND), IC2.24 (2~OE), IC2.28 (GND), IC2.34 (GND), IC2.39 (GND), IC2.45 (GND), IC3.4 (GND), IC4.2 (GND), IC5.8 (GND), IC6.3 (D0), IC6.4 (D1), IC6.6 (D3), IC6.8 (GND), IC7.2 (GND), J1.5, J1.12, J1.21, J1.28
Selected Pattern: IC3.3 (2Y), J1.31
TC: IC4.1 (1A), IC6.15 (TC), J1.30
Write Pattern High: IC2.25 (2LE), J1.7
Write Pattern Low: IC2.48 (1LE), J1.6
~Reset: IC3.2 (1B), J1.2

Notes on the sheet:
C15 C14 C13 C12 C11 C10 C9 C8 C7 C6 C5 C4
DH7 DH6 DH5 DH4 DH3 DH2 DH1 DH0 DL3 DL2 DL1 DL0
→ RPS0 → RPS1 → RPS2 → RPS3 → RPS4 → RPS5 → RPS6 → RPS7 → RPS8 → RPS9 → RPS10 → RPS11

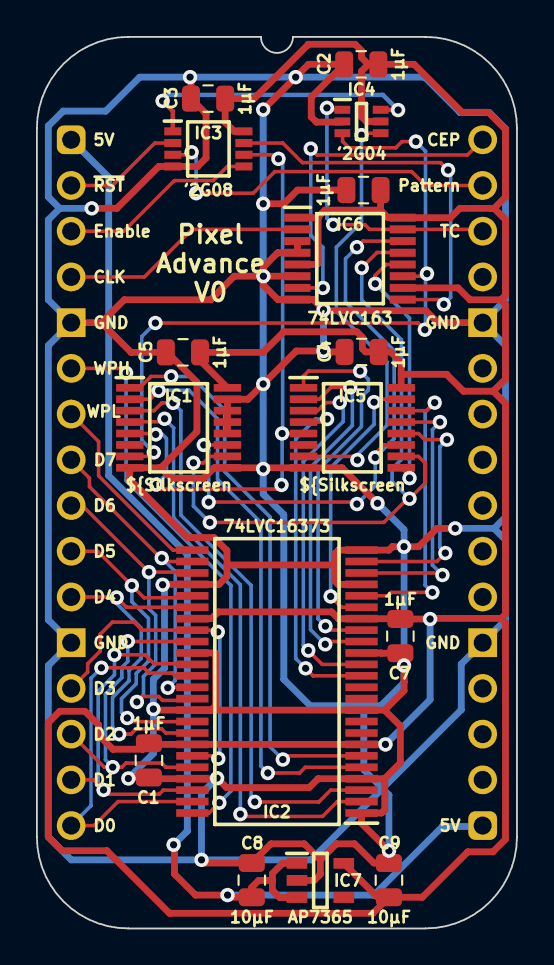
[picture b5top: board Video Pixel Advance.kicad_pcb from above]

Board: 2 copper layers, 26.7 x 49.5 mm, 17 parts (0 on the bottom side), 39 nets.
